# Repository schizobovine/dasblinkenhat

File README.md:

# dasblinkenhat
Using an ATTiny85 and a NeoPixel strip, an attempt to fix a silly hat and make it even sillier.

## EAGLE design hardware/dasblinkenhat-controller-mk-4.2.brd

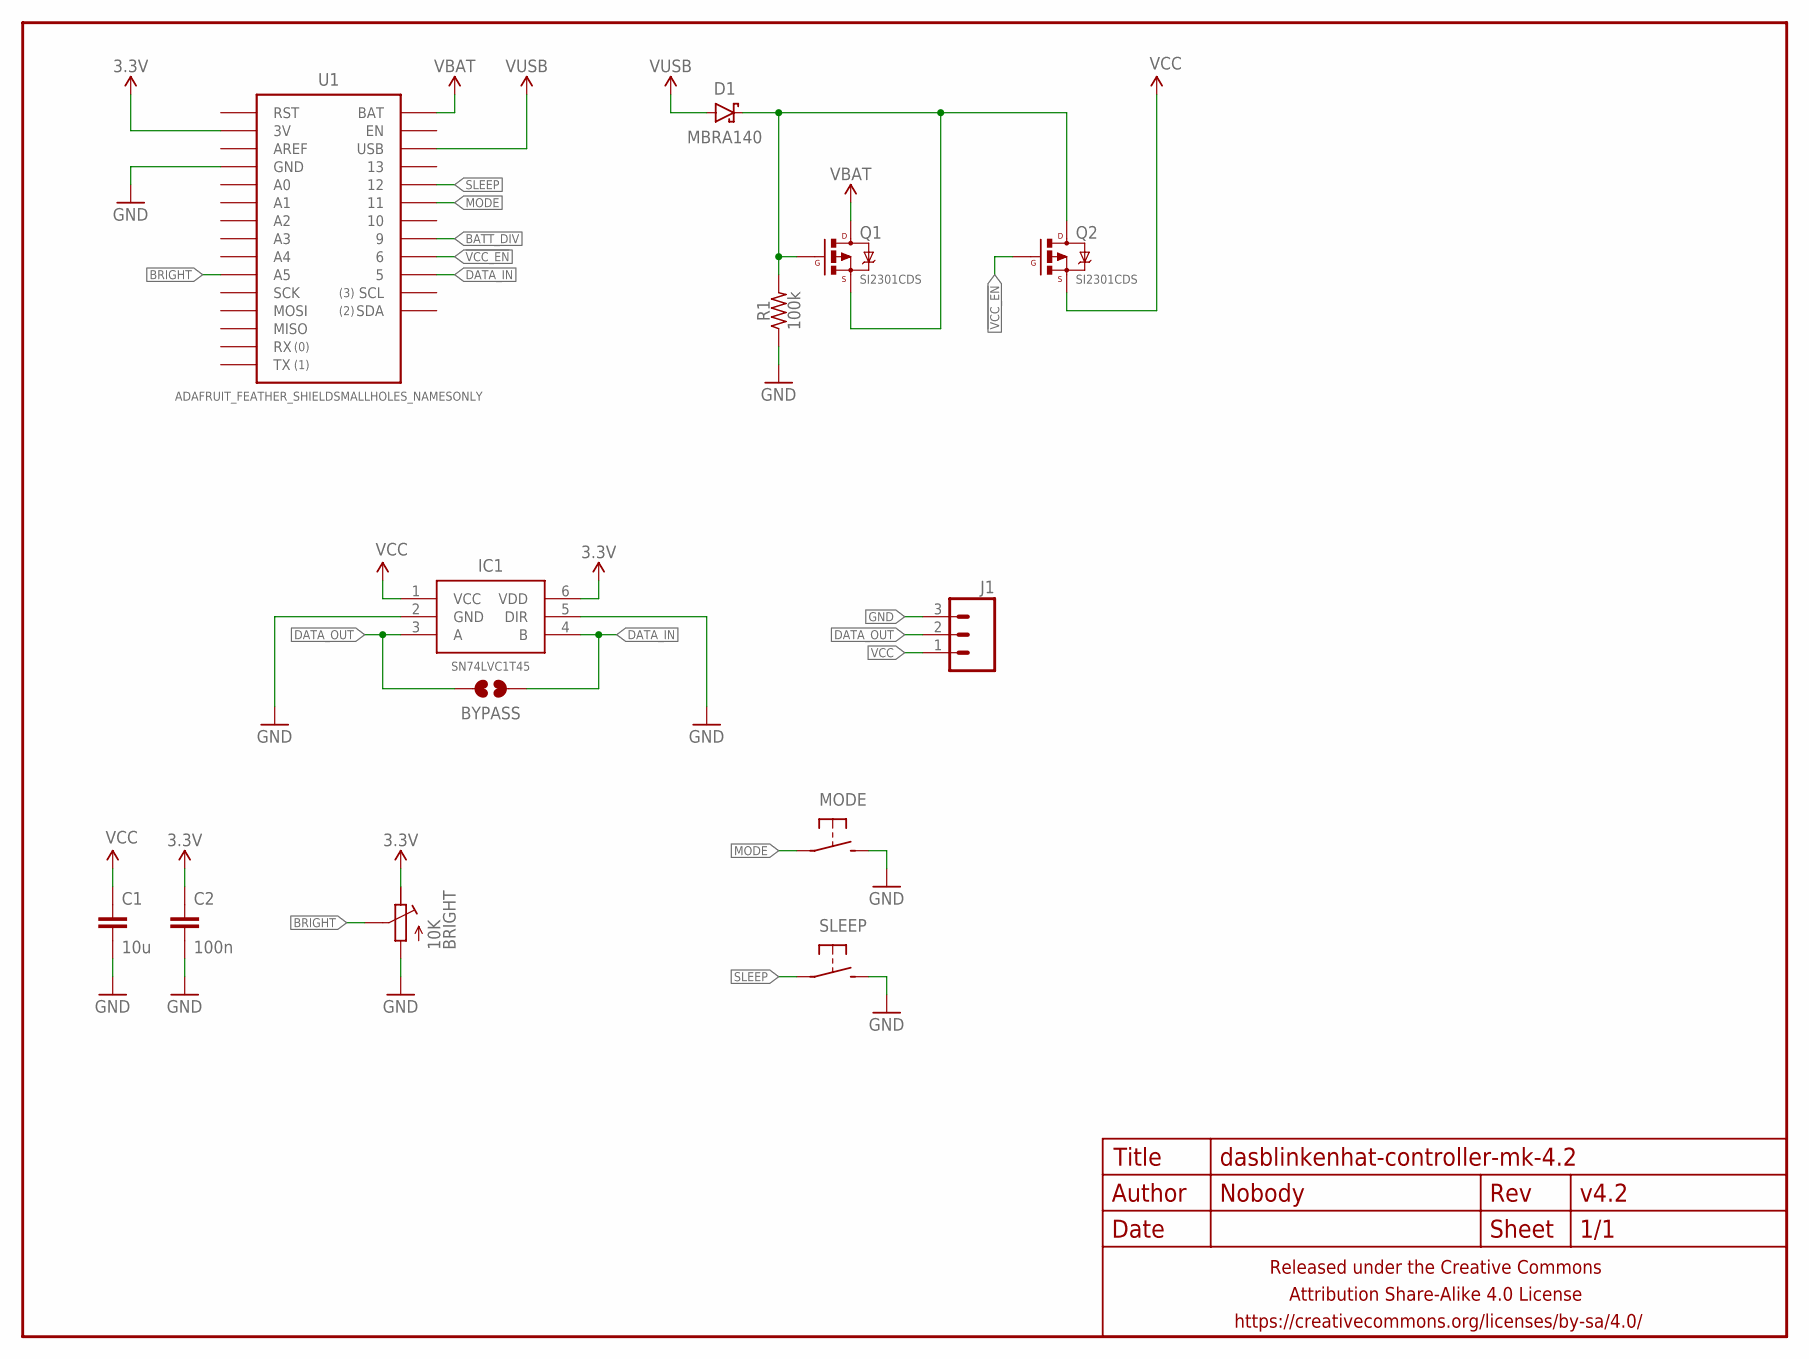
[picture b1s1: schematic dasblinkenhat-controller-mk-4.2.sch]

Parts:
BRIGHT: 10K; EVM3Y
BYPASS: JUMPER-PAD-2-NOYES_SILK; PAD-JUMPER-2-NO_YES_SILK
C1: 10u; C0805
C2: 100n; C0603
D1: MBRA140; SMA-DIODE
FRAME1: FRAME-LETTERNO_PACKAGE; DUMMY
IC1: SN74LVC1T45; SOT23-6
J1: M03JST-XH-RA-PTH; JST-3-XH-RA-PTH
MODE: DTS-6MM; TACTILE-PTH-12MM
Q1, Q2: SI2301CDS; SOT23
R1: 100k; R0603
SLEEP: DTS-6MM; TACTILE-PTH-12MM
U1: ADAFRUIT_FEATHER_SHIELDSMALLHOLES_NAMESONLY; ADAFRUIT_FEATHER_SMALLHOLES_NAMESONLY

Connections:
3.3V: BRIGHT.E, C2.1, IC1.6 (VDD), U1.3V
!VCC_EN: Q2.1 (G), U1.6
BATT_DIV: U1.9
BRIGHT: BRIGHT.S, U1.A5
DATA_IN: BYPASS.1, IC1.4 (B), U1.5
DATA_OUT: BYPASS.2, IC1.3 (A), J1.2
GND: BRIGHT.A, C1.2, C2.2, IC1.2 (GND), IC1.5 (DIR), J1.3, MODE.3 (2), MODE.4 (2), R1.1, SLEEP.3 (2), SLEEP.4 (2), U1.GND@0 (GND), U1.GND@1 (GND)
MODE: MODE.1, MODE.2 (1), U1.11
unnamed: D1.C, Q1.1 (G), Q1.2 (S), Q2.3 (D), R1.2
SLEEP: SLEEP.1, SLEEP.2 (1), U1.12
VBAT: Q1.3 (D), U1.BAT
VCC: C1.1, IC1.1 (VCC), J1.1, Q2.2 (S)
VUSB: D1.A, U1.USB

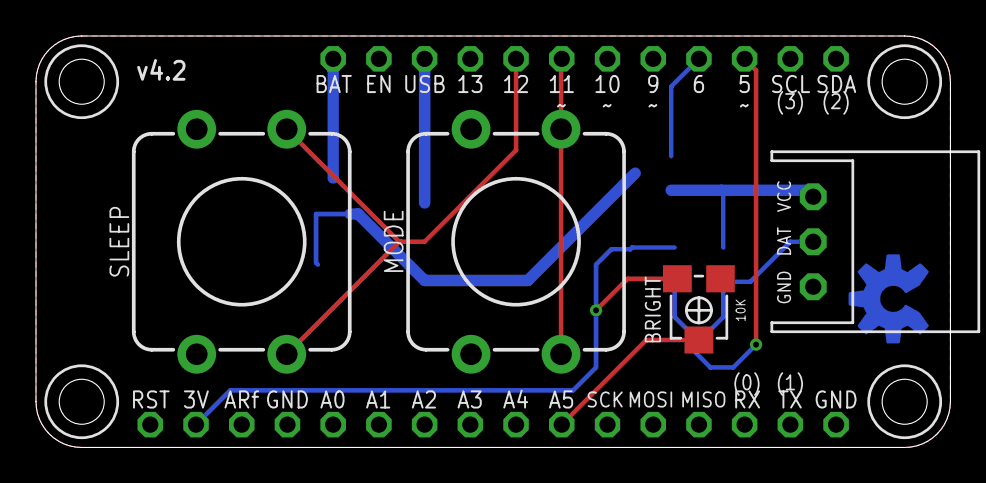
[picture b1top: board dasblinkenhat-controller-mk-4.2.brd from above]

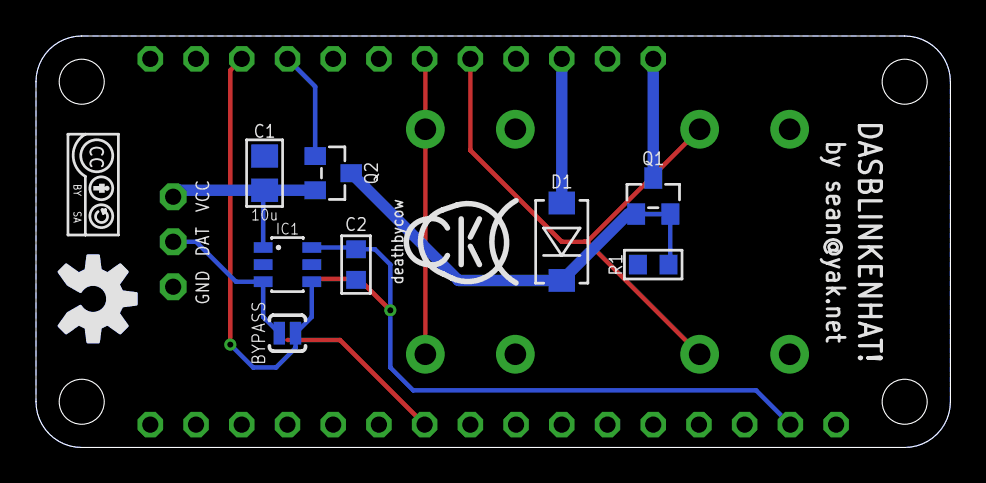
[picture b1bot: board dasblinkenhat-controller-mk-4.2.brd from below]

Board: 2 copper layers, 50.8 x 22.9 mm, 17 parts (11 on the bottom side), 12 nets.

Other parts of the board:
U$1: CC-BY-SA-4.0-NO-URL
U$3: OSHWLOGO_5MM_METAL
U$4: COW_SMALL

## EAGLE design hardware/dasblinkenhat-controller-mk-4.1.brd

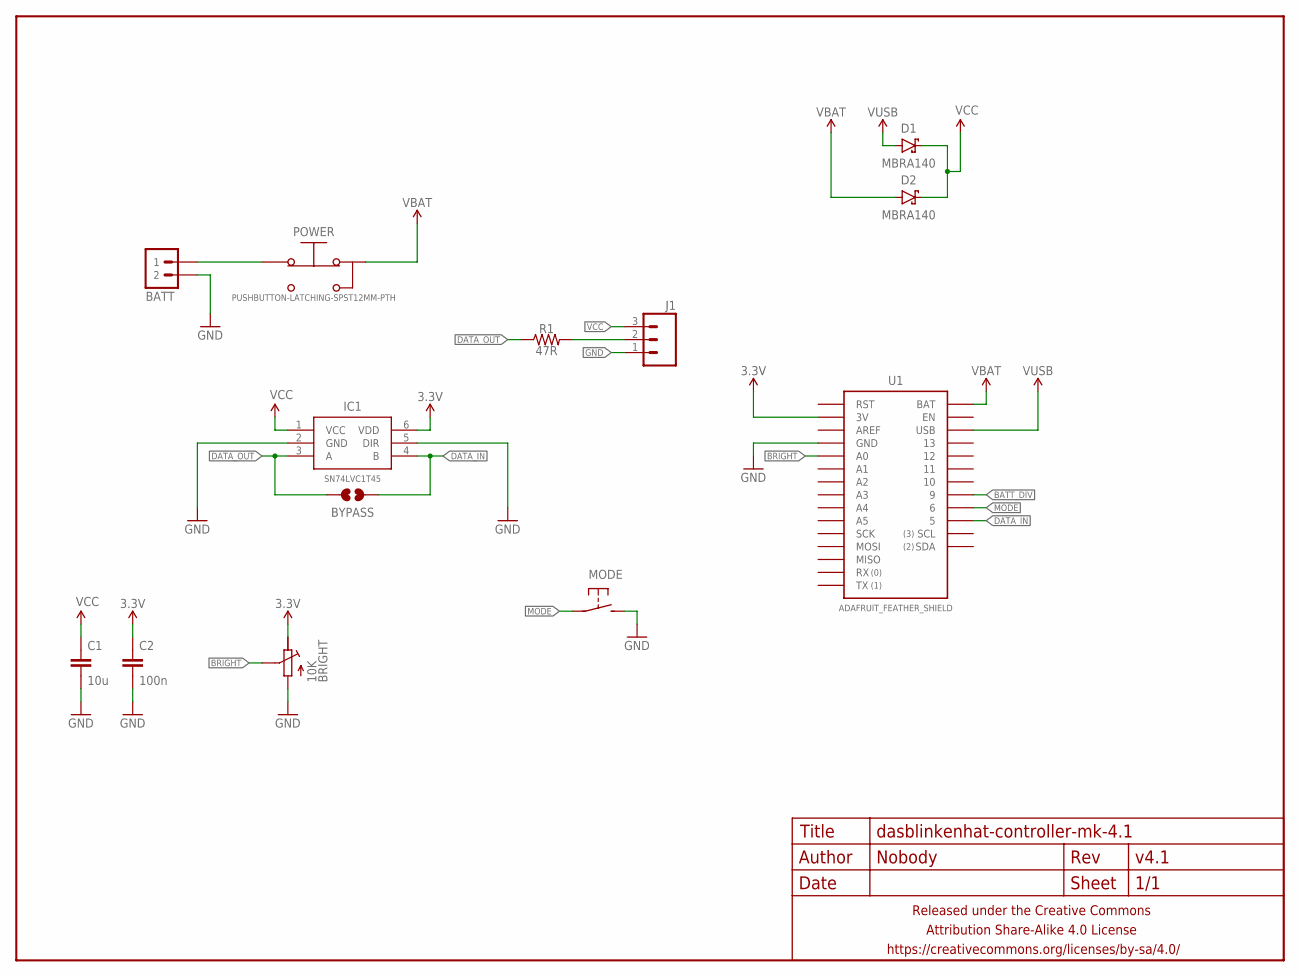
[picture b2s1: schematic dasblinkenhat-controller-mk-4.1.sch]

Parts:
BATT: M02JST-2MM-SMT; JST-2-SMD
BRIGHT: 10K; EVM3Y
BYPASS: JUMPER-PAD-2-NOYES_SILK; PAD-JUMPER-2-NO_YES_SILK
C1: 10u; C0805
C2: 100n; C0603
D1, D2: MBRA140; SMA-DIODE
FRAME1: FRAME-LETTERNO_PACKAGE; DUMMY
IC1: SN74LVC1T45; SOT23-6
J1: M03JST-XH-RA-PTH; JST-3-XH-RA-PTH
MODE: DTS-6MM; TACTILE-PTH-12MM
POWER: PUSHBUTTON-LATCHING-SPST12MM-PTH; PUSHBUTTON-CW-SPST-12MM
R1: 47R; R0603
U1: ADAFRUIT_FEATHER_SHIELD; ADAFRUIT_FEATHER

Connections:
3.3V: BRIGHT.E, C2.1, IC1.6 (VDD), U1.3V
BATT_DIV: U1.9
BRIGHT: BRIGHT.S, U1.A0
DATA_IN: BYPASS.1, IC1.4 (B), U1.5
DATA_OUT: BYPASS.2, IC1.3 (A), R1.1
GND: BATT.1 (2), BRIGHT.A, C1.2, C2.2, IC1.2 (GND), IC1.5 (DIR), J1.1, MODE.3 (2), MODE.4 (2), U1.GND@0 (GND), U1.GND@1 (GND)
MODE: MODE.1, MODE.2 (1), U1.6
unnamed: BATT.2 (1), POWER.2 (NC)
unnamed: J1.2, R1.2
VBAT: D2.A, POWER.1 (COM), U1.BAT
VCC: C1.1, D1.C, D2.C, IC1.1 (VCC), J1.3
VUSB: D1.A, U1.USB

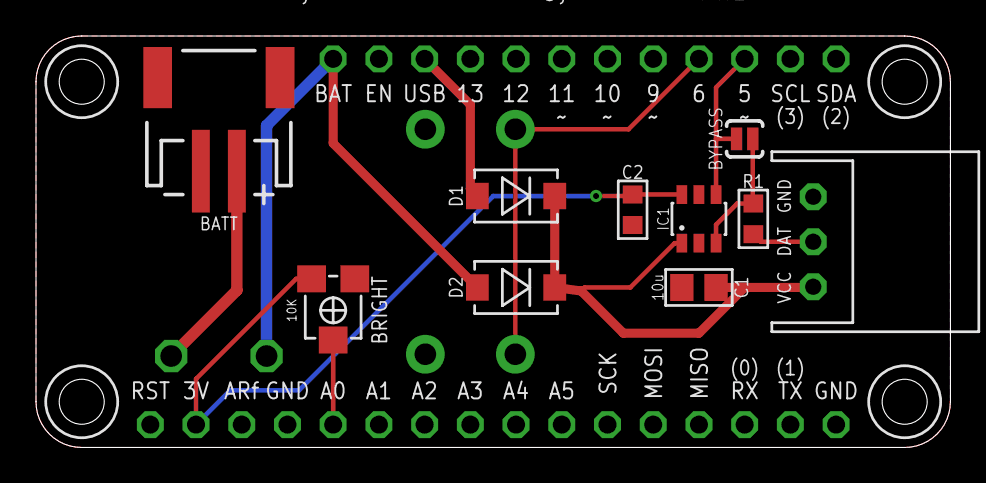
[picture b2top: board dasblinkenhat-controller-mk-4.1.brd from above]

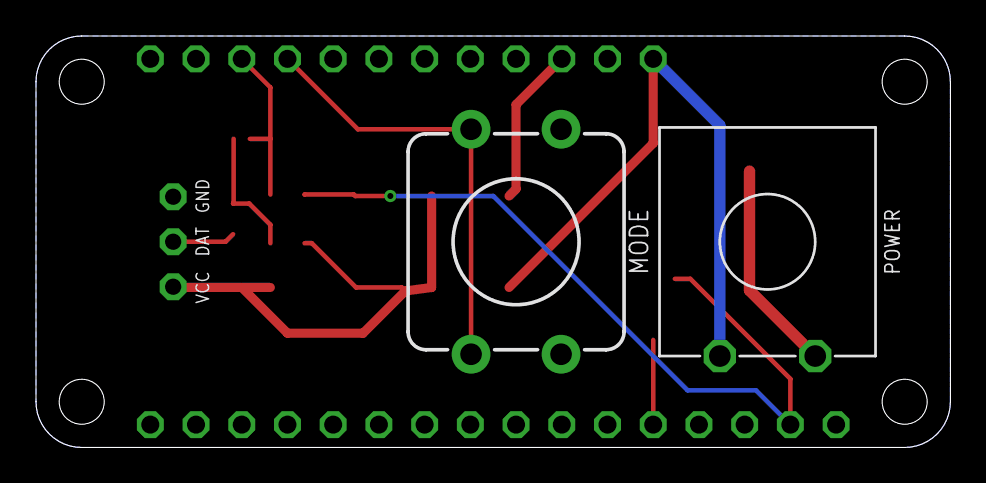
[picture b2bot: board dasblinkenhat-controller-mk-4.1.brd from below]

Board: 2 copper layers, 50.8 x 22.9 mm, 15 parts (3 on the bottom side), 11 nets.

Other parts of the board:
U$2: OSHWLOGO_TINY_SILKONLY

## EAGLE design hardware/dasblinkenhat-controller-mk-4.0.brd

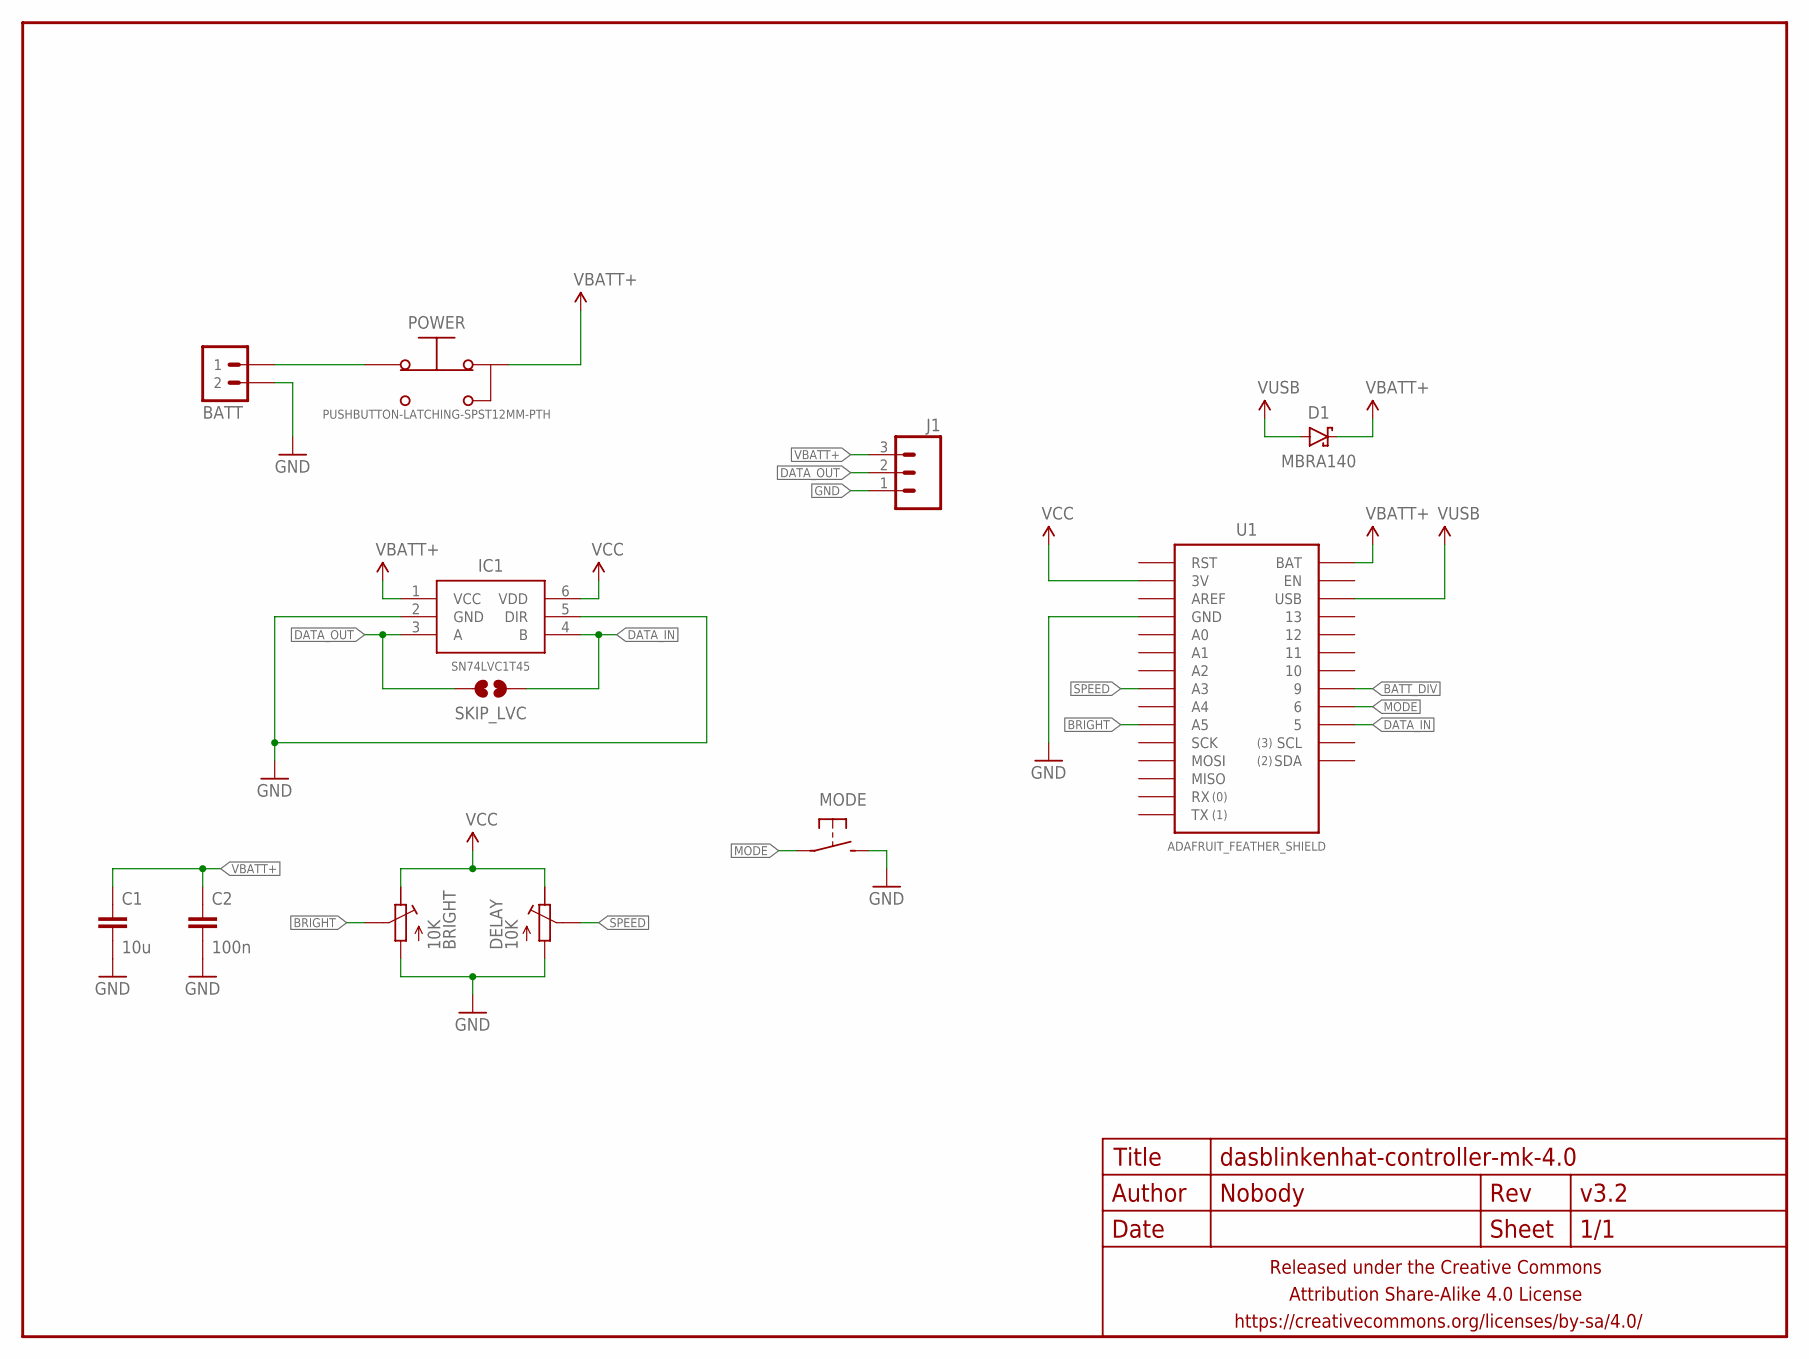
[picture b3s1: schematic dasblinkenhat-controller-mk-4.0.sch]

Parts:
BATT: M02JST-2MM-SMT; JST-2-SMD
BRIGHT: 10K; EVM3Y
C1: 10u; C0805
C2: 100n; C0805
D1: MBRA140; SMA-DIODE-SCHOTTKY
DELAY: 10K; EVM3Y
FRAME1: FRAME-LETTERNO_PACKAGE; DUMMY
IC1: SN74LVC1T45; SOT23-6
J1: M03JST-XH-RA-PTH; JST-3-XH-RA-PTH
MODE: DTS-6MM; DTSM-6
POWER: PUSHBUTTON-LATCHING-SPST12MM-PTH; PUSHBUTTON-CW-SPST-12MM
SKIP_LVC: JUMPER-PAD-2-NOYES_SILK; PAD-JUMPER-2-NO_YES_SILK
U1: ADAFRUIT_FEATHER_SHIELD; ADAFRUIT_FEATHER

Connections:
BATT_DIV: U1.9
BRIGHT: BRIGHT.S, U1.A5
DATA_IN: IC1.4 (B), SKIP_LVC.1, U1.5
DATA_OUT: IC1.3 (A), J1.2, SKIP_LVC.2
GND: BATT.1 (2), BRIGHT.A, C1.2, C2.2, DELAY.A, IC1.2 (GND), IC1.5 (DIR), J1.1, MODE.3 (2), MODE.4 (2), U1.GND@0 (GND), U1.GND@1 (GND)
MODE: MODE.1, MODE.2 (1), U1.6
unnamed: BATT.2 (1), POWER.2 (NC)
SPEED: DELAY.S, U1.A3
VBATT+: C1.1, C2.1, D1.C, IC1.1 (VCC), J1.3, POWER.1 (COM), U1.BAT
VCC: BRIGHT.E, DELAY.E, IC1.6 (VDD), U1.3V
VUSB: D1.A, U1.USB

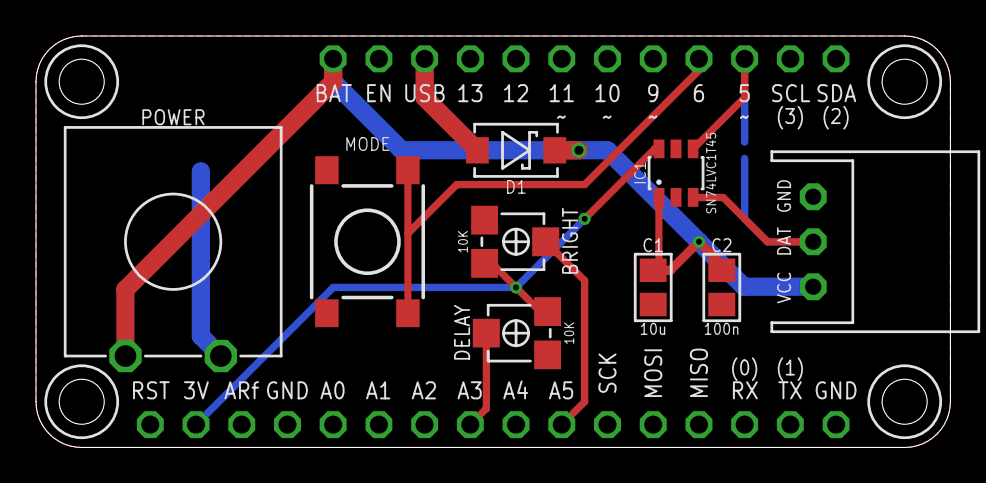
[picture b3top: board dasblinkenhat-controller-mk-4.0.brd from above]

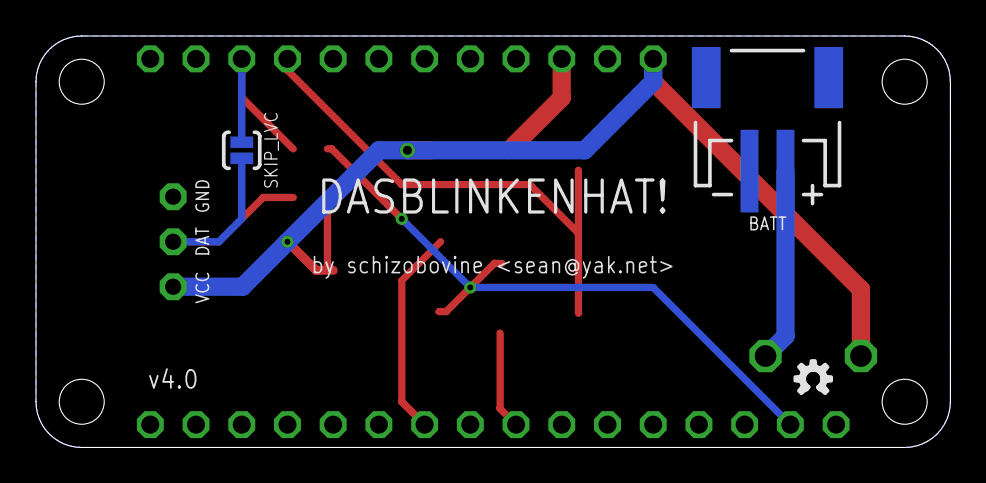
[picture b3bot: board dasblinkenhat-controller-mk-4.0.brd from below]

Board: 2 copper layers, 50.8 x 22.9 mm, 14 parts (3 on the bottom side), 10 nets.

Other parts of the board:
U$2: OSHWLOGO_TINY_SILKONLY

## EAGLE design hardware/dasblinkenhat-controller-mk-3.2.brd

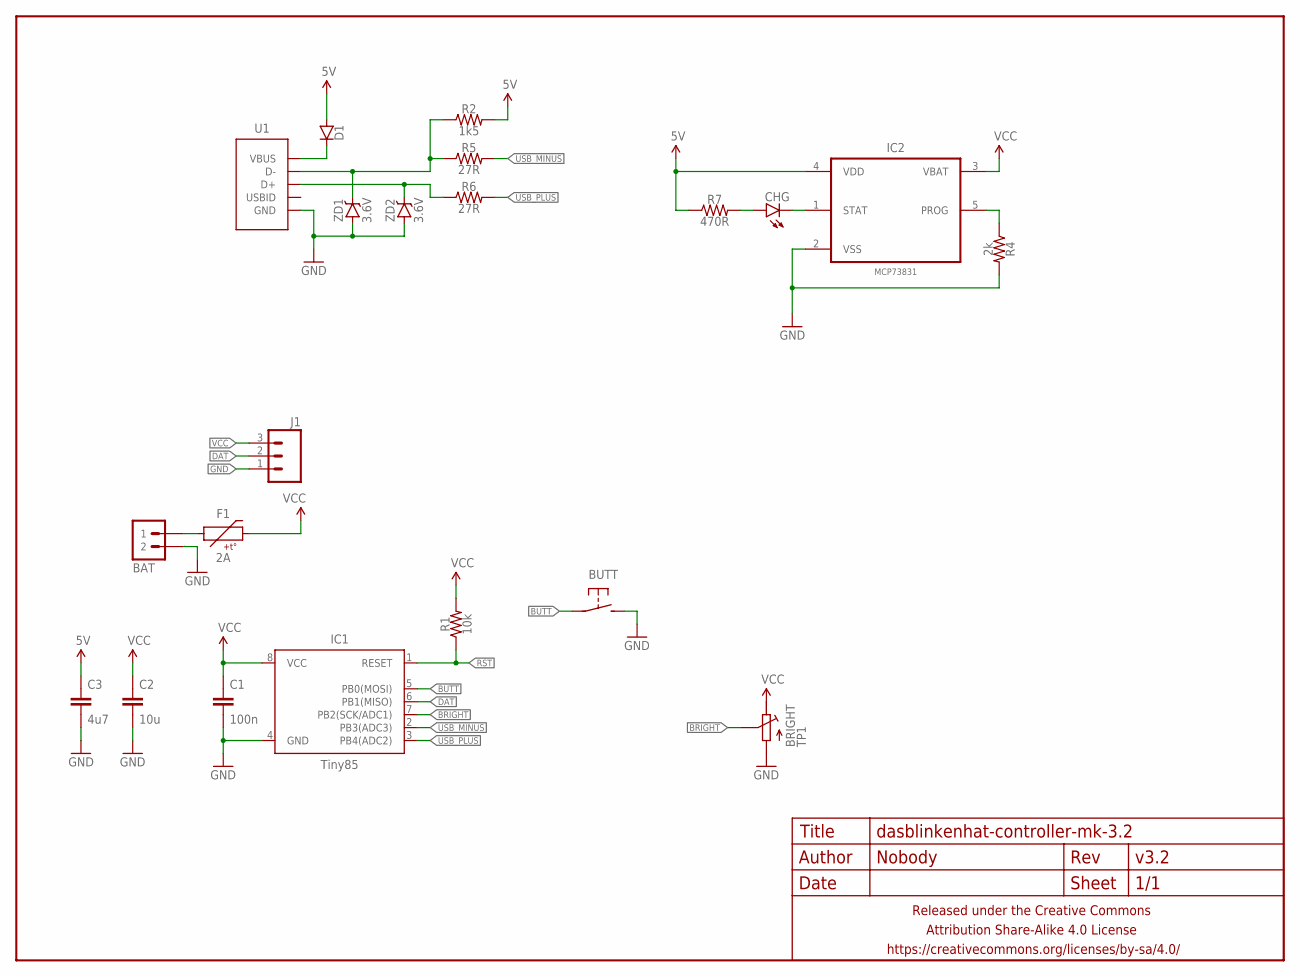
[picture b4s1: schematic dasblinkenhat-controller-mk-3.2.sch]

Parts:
BAT: M02JST-2MM-SMT; JST-2-SMD
BUTT: DTS-6MM; DTSM-6
C1: 100n; C0603
C2: 10u; C0805
C3: 4u7; C0805
CHG: LED0603; LED-0603
D1: DIODESOD123; SOD123
F1: 2A; PTC-1206
FRAME1: FRAME-LETTERNO_PACKAGE; DUMMY
IC1: Tiny85; SO08-EIAJ
IC2: MCP73831; SOT95P280X145-5N
J1: M03JST-XH-RA-PTH; JST-3-XH-RA-PTH
R1: 10k; R0603
R2: 1k5; R0603
R4: 2k; R0603
R5, R6: 27R; R0603
R7: 470R; R0603
TP1: BRIGHT; EVM3Y
U1: USB-ABFCI-10103594-USB-MICRO-B-LESS; FCI-10103594-USB-MICRO-B-LESS
ZD1, ZD2: 3.6V; SOD323-ZENNER

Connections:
5V: C3.1, D1.A, IC2.4 (VDD), R2.2, R7.1
BRIGHT: IC1.7 (PB2(SCK/ADC1)), TP1.S
BUTT: BUTT.1, BUTT.2 (1), IC1.5 (PB0(MOSI))
DAT: IC1.6 (PB1(MISO)), J1.2
GND: BAT.1 (2), BUTT.3 (2), BUTT.4 (2), C1.2, C2.2, C3.2, IC1.4 (GND), IC2.2 (VSS), J1.1, R4.2, TP1.A, U1.5 (GND), ZD1.A, ZD2.A
unnamed: BAT.2 (1), F1.1
unnamed: D1.C, U1.1 (VBUS)
unnamed: IC2.5 (PROG), R4.1
unnamed: R2.1, R5.1, U1.2 (D-), ZD1.C
unnamed: R6.1, U1.3 (D+), ZD2.C
unnamed: CHG.A, R7.2
unnamed: CHG.C, IC2.1 (STAT)
RST: IC1.1 (RESET), R1.1
USB_MINUS: IC1.2 (PB3(ADC3)), R5.2
USB_PLUS: IC1.3 (PB4(ADC2)), R6.2
VCC: C1.1, C2.1, F1.2, IC1.8 (VCC), IC2.3 (VBAT), J1.3, R1.2, TP1.E

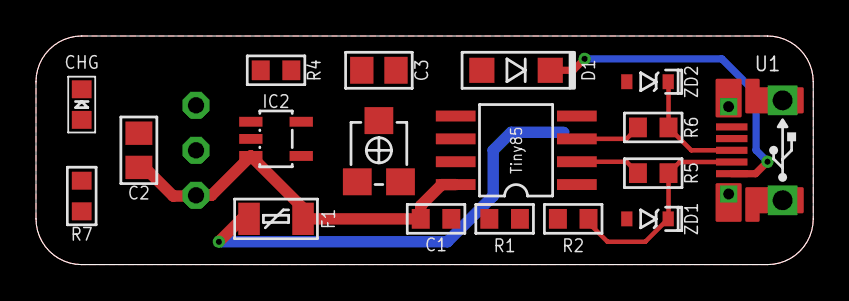
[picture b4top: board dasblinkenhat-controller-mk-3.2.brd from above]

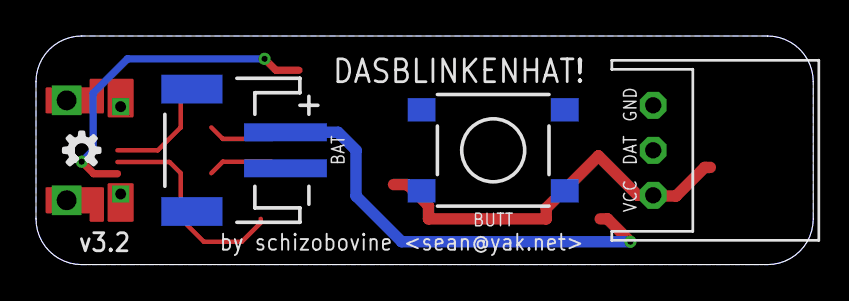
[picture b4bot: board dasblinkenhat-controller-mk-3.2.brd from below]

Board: 2 copper layers, 43.2 x 12.7 mm, 23 parts (4 on the bottom side), 16 nets.

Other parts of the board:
U$2: OSHWLOGO_TINY_SILKONLY

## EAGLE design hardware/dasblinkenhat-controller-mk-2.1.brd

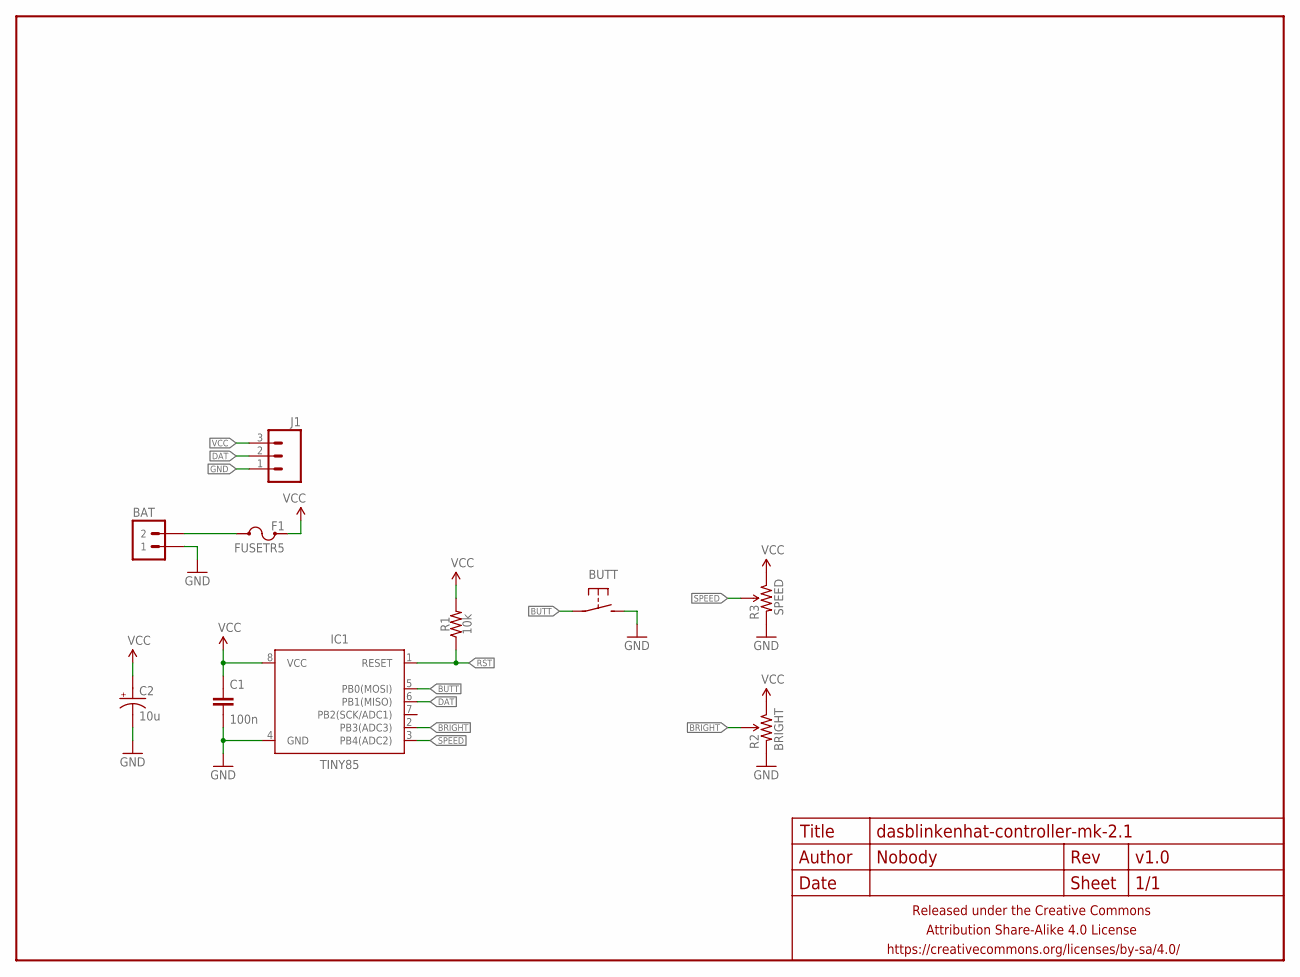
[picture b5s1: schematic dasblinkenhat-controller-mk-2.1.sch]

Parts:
BAT: M02JST-PTH-RA-R+; JST-2-PH-RA-PTH-R+
BUTT: DTS-6MM; DTS-6-SMALL-PADS
C1: 100n; C025-024X044
C2: 10u; E2-5
F1: FUSETR5; TR5
FRAME1: FRAME-LETTERNO_PACKAGE; DUMMY
IC1: TINY85; DIP08
J1: M03JST-XH-RA-PTH; JST-3-XH-RA-PTH
R1: 10k; RESISTOR-AXIAL-PTH-5.08MM
R2: BRIGHT; TRIM_POT_PTH2
R3: SPEED; TRIM_POT_PTH2

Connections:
BRIGHT: IC1.2 (PB3(ADC3)), R2.2 (WIPER)
BUTT: BUTT.1, BUTT.2 (1), IC1.5 (PB0(MOSI))
DAT: IC1.6 (PB1(MISO)), J1.2
GND: BAT.1, BUTT.3 (2), BUTT.4 (2), C1.2, C2.-, IC1.4 (GND), J1.1, R2.3 (CW), R3.3 (CW)
unnamed: BAT.2, F1.2
RST: IC1.1 (RESET), R1.P$1 (1)
SPEED: IC1.3 (PB4(ADC2)), R3.2 (WIPER)
VCC: C1.1, C2.+, F1.1, IC1.8 (VCC), J1.3, R1.P$2 (2), R2.1 (CCW), R3.1 (CCW)

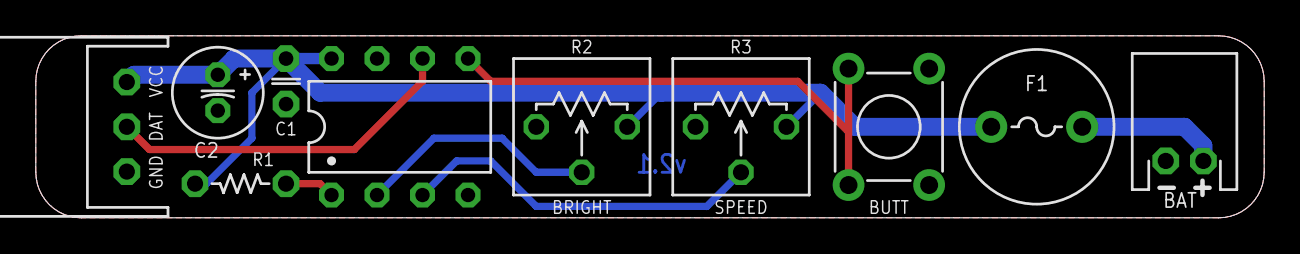
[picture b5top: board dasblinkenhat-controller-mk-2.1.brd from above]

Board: 2 copper layers, 68.6 x 10.2 mm, 12 parts (1 on the bottom side), 8 nets.

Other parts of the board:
U$2: OSHWLOGO_TINY_SILKONLY

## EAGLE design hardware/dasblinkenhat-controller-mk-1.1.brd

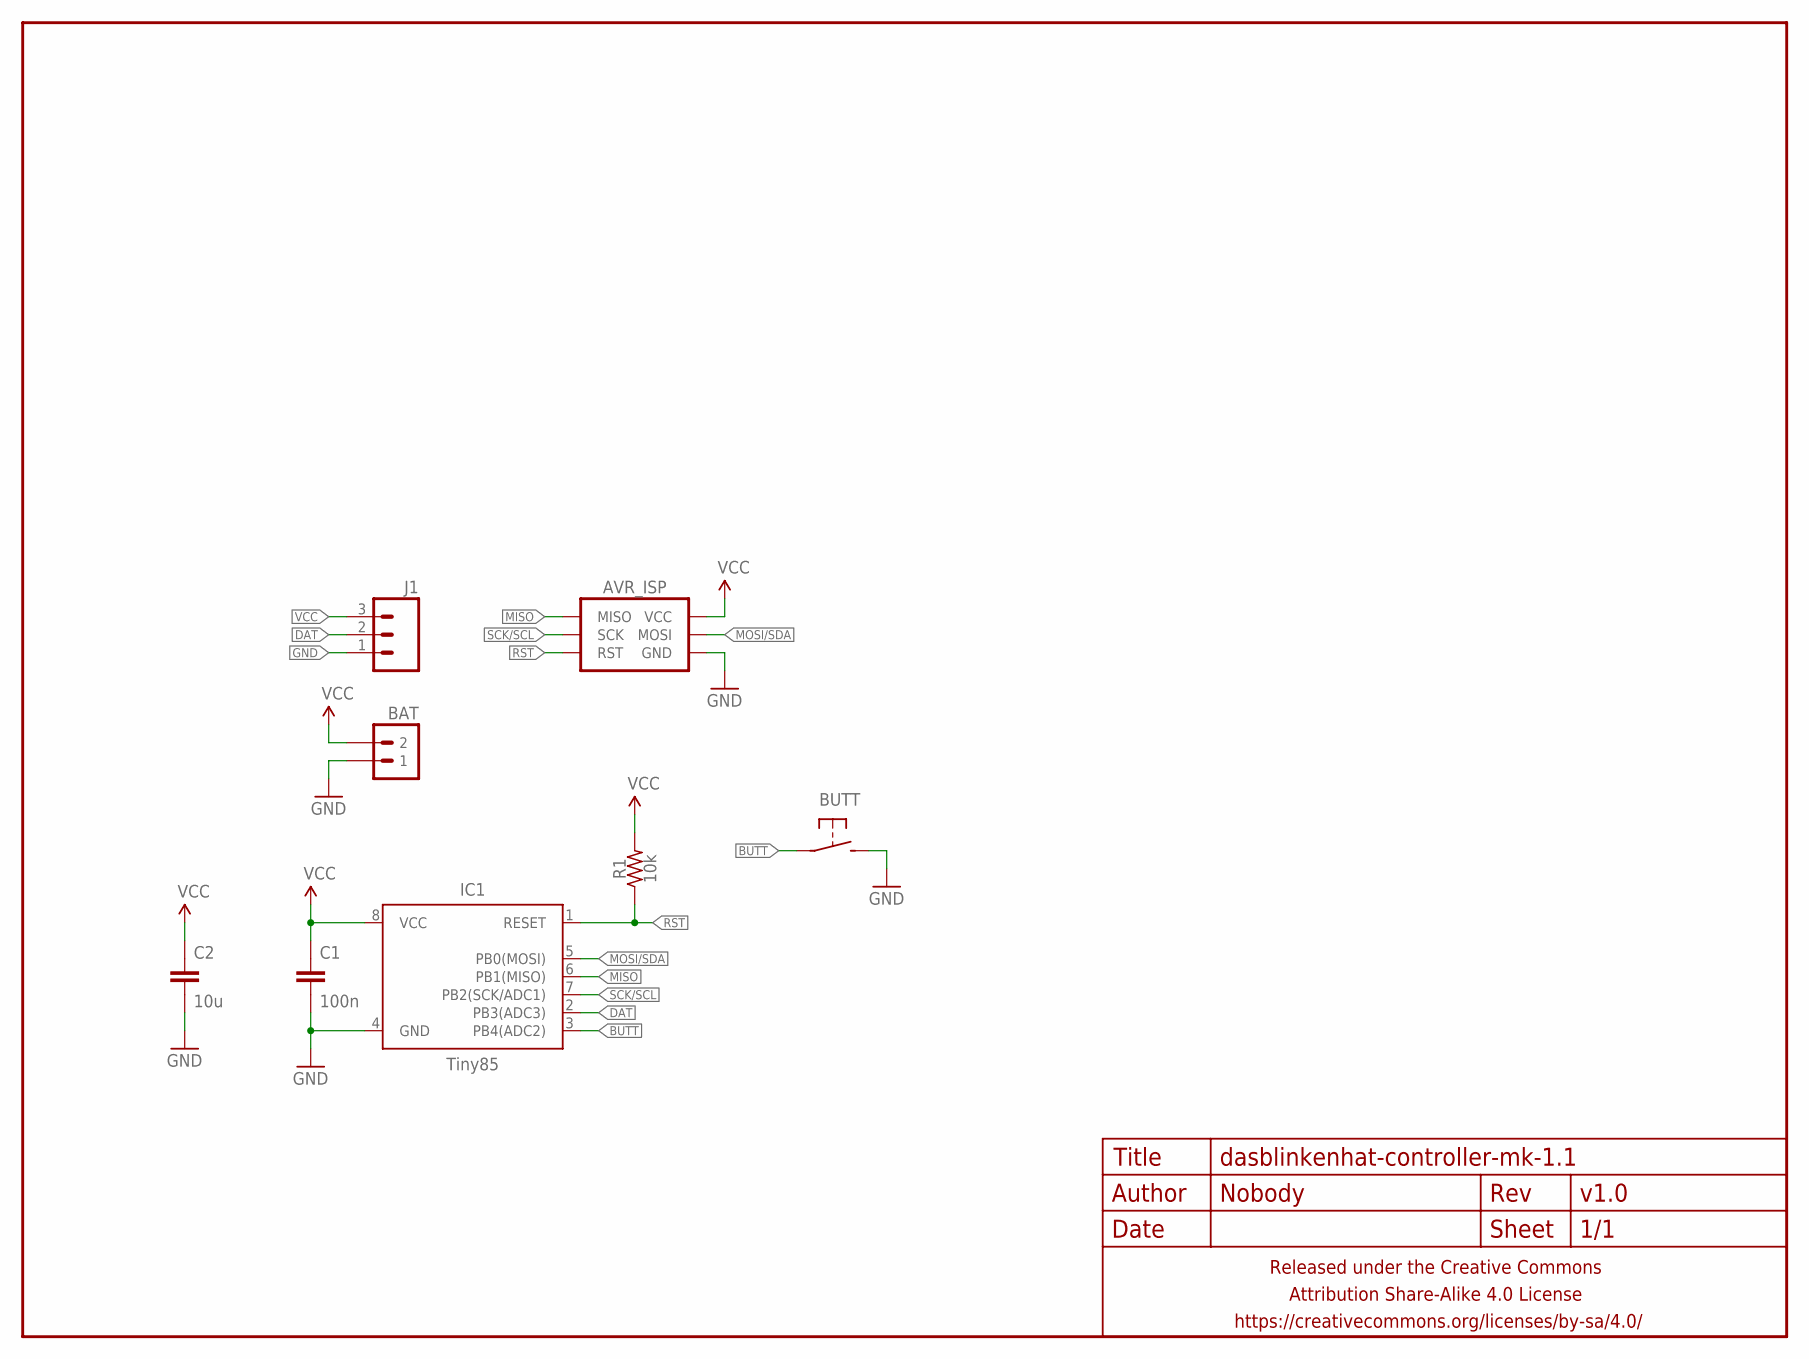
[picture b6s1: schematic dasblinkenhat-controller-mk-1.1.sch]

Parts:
AVR_ISP: AVR_SPI_PRG_6TESTPOINTS; 2X3_TEST_POINTS
BAT: M02JST-2MM-SMT; JST-2-SMD
BUTT: DTS-6MM; TACTILE-SWITCH-SMD
C1: 100n; C0603
C2: 10u; C0805
FRAME1: FRAME-LETTERNO_PACKAGE; DUMMY
IC1: Tiny85; SO08-EIAJ
J1: M03JST-XH-RA-PTH; JST-3-XH-RA-PTH
R1: 10k; R0603

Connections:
BUTT: BUTT.A@1 (1), BUTT.A@2 (1), IC1.3 (PB4(ADC2))
DAT: IC1.2 (PB3(ADC3)), J1.2
GND: AVR_ISP.6 (GND), BAT.2 (1), BUTT.B@1 (2), BUTT.B@2 (2), C1.2, C2.2, IC1.4 (GND), J1.1
MISO: AVR_ISP.1 (MISO), IC1.6 (PB1(MISO))
MOSI/SDA: AVR_ISP.4 (MOSI), IC1.5 (PB0(MOSI))
RST: AVR_ISP.5 (RST), IC1.1 (RESET), R1.1
SCK/SCL: AVR_ISP.3 (SCK), IC1.7 (PB2(SCK/ADC1))
VCC: AVR_ISP.2 (VCC), BAT.1 (2), C1.1, C2.1, IC1.8 (VCC), J1.3, R1.2

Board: 2 copper layers, 9 parts (2 on the bottom side), 8 nets, no tracks yet.

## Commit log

2016-03-20 adding submodules
2016-03-20 inital checking
2016-03-21 dual modes
2016-03-28 new controller board stick
2016-03-28 minor silk tweak
2016-03-28 added fuse
2016-03-28 smt version
2016-04-01 smd layouts
2016-04-01 smd layouts pt 2
2016-04-01 repinning for prototype and brightness setting
2016-04-08 add waterfall feature
2016-04-08 new board rev
2016-04-08 working 4 mode feather based woo!
2016-04-13 new hardware rev off to fab
2016-04-15 rework waterfall routine so no more off by one error
2016-07-09 add backflow diode, proper level shifter
2016-07-09 ditch hard battery control, allow soft-power off
2016-07-09 change pin assignments
2016-07-10 bluefruit it up
2016-07-10 try to add ble
2016-07-10 attempt to satisfy gods of bad dir naming conventions
2016-07-11 once again working
2016-10-01 resync with upstream
2016-10-12 remove bt support as was adding too much pain in the ass

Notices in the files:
parts and their libraries:
a_parts: Released under the Creative Commons Attribution Share-Alike 4.0 License
a_parts: https://creativecommons.org/licenses/by-sa/4.0
a_parts: Released under the Creative Commons
